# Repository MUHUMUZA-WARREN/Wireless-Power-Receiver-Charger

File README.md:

# Wireless-Power-Receiver---Charger
 5W resonant wireless power receiver and charger

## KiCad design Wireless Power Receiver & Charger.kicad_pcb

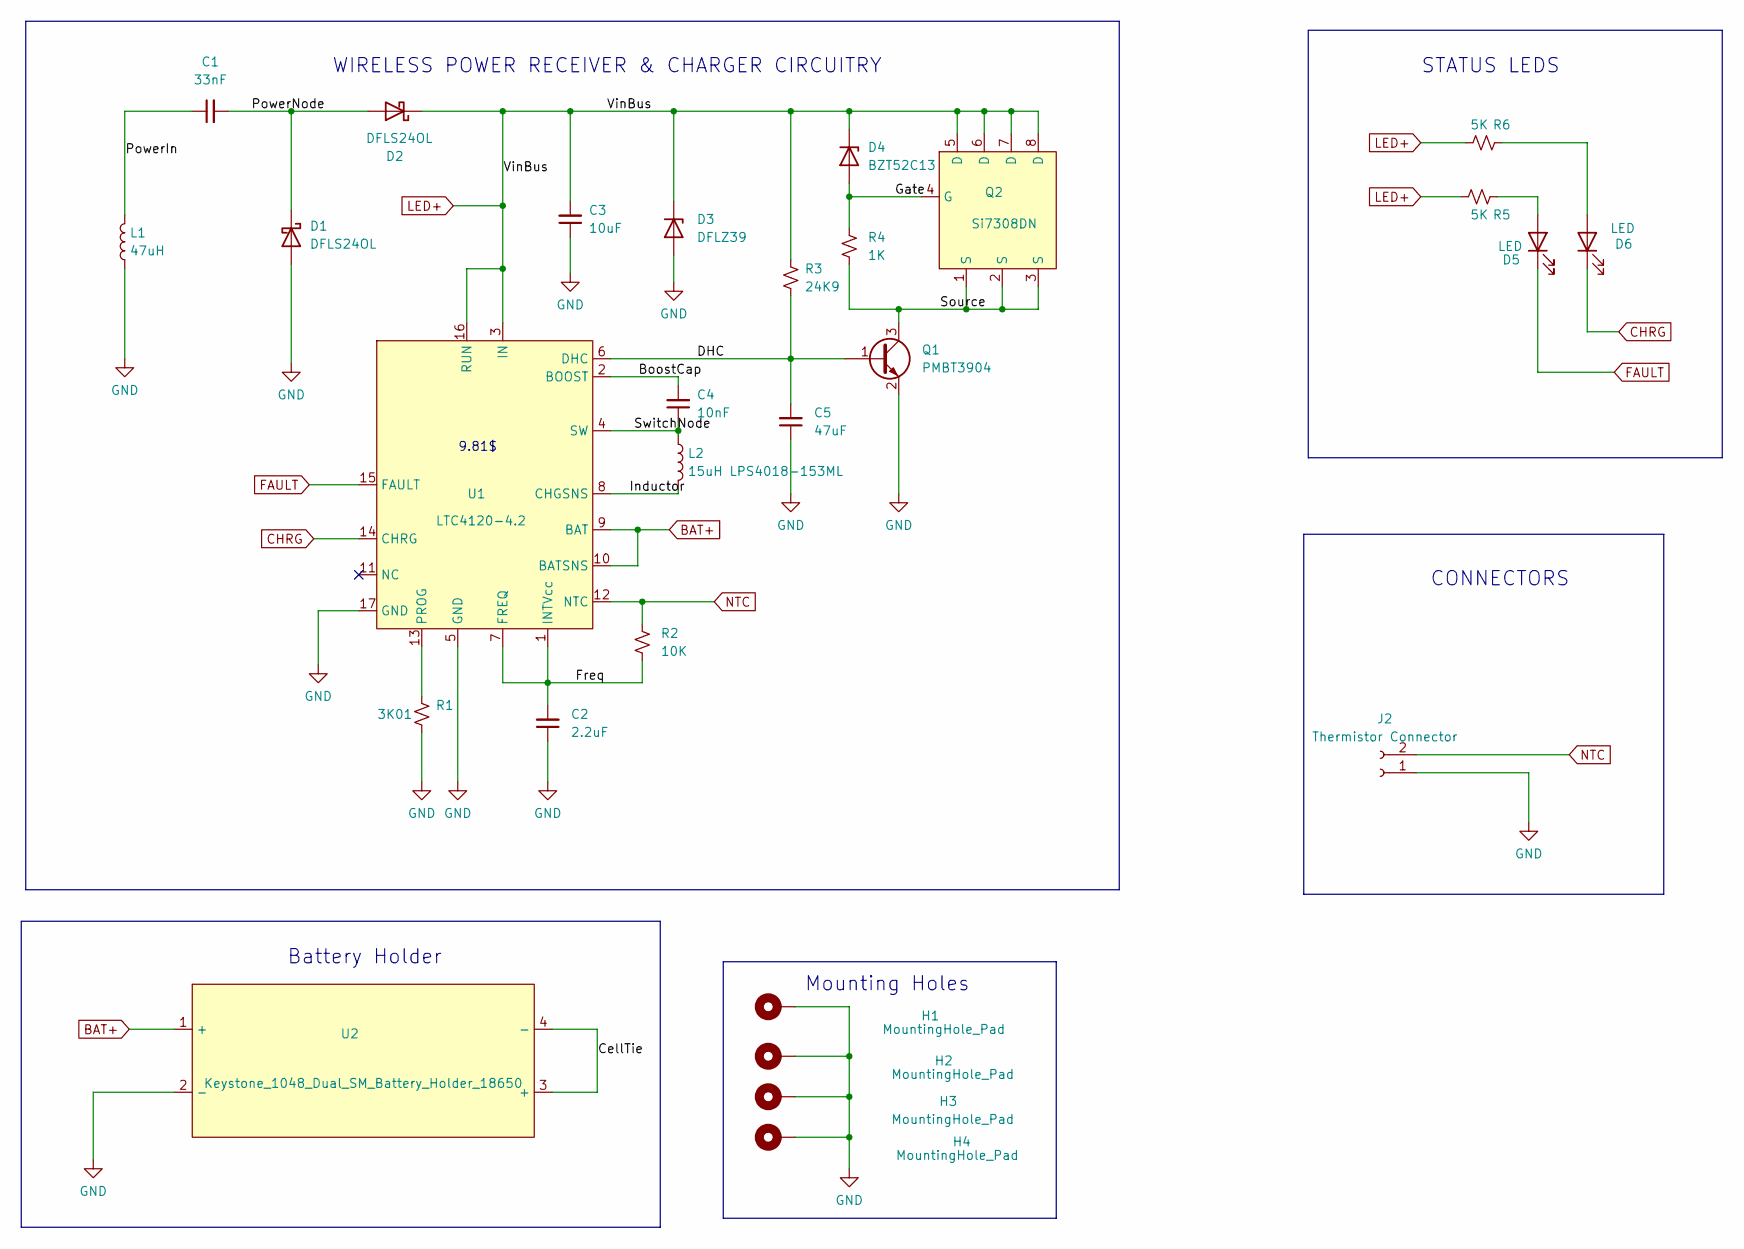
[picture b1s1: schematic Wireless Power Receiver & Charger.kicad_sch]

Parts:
C1: 33nF; C_1206_3216Metric
C2: 2.2uF; C_1206_3216Metric
C3: 10uF; C_1206_3216Metric
C4: 10nF; C_1206_3216Metric
C5: 47uF; C_0805_2012Metric
D1, D2: DFLS24OL; D_PowerDI-123
D3: DFLZ39; D_PowerDI-123
D4: BZT52C13; D_SOD-123
D5, D6: LED; LED_D1.8mm_W1.8mm_H2.4mm_Horizontal_O1.27mm_Z1.6mm
H1, H2, H3, H4: MountingHole_Pad; MountingHole_2.5mm_Pad_Via
J2: Thermistor Connector; JST_EH_B2B-EH-A_1x02_P2.50mm_Vertical
L1: 47uH; Tx Coil
L2: 15uH LPS4018-153ML; L_Coilcraft_LPS4018
Q1: PMBT3904; TSOT-23
Q2: Si7308DN; PowerPAK 1212-8 Single
R1: 3K01; R_1206_3216Metric
R2: 10K; R_1206_3216Metric
R3: 24K9; R_0805_2012Metric
R4: 1K; R_1206_3216Metric
R5, R6: 5K; R_1206_3216Metric
U1: LTC4120-4.2; QFN-16-1EP_4x4mm_P0.65mm_EP2.1x2.1mm_ThermalVias
U2: Keystone_1048_Dual_SM_Battery_Holder_18650; 1048 Dual SM Battery Holder 18650

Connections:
/BoostCap: C4.2, U1.2 (BOOST)
/CellTie: U2.3 (+), U2.4 (-)
/DHC: C5.2, Q1.1 (B), R3.2, U1.6 (DHC)
/Freq: C2.2, R2.2, U1.1 (INTVcc), U1.7 (FREQ)
/Gate: D4.2 (A), Q2.4 (G), R4.1
/Inductor: L2.2, U1.8 (CHGSNS)
/PowerIn: C1.1, L1.2
/PowerNode: C1.2, D1.1 (K), D2.2 (A)
/Source: Q1.3 (C), Q2.1 (S), Q2.2 (S), Q2.3 (S), R4.2
/SwitchNode: C4.1, L2.1, U1.4 (SW)
BAT+: U1.9 (BAT), U1.10 (BATSNS), U2.1 (+)
CHRG: D6.1 (K), U1.14 (CHRG)
FAULT: D5.1 (K), U1.15 (FAULT)
GND: C2.1, C3.1, C5.1, D1.2 (A), D3.2 (A), H1.1, H2.1, H3.1, H4.1, J2.1, L1.1, Q1.2 (E), R1.2, U1.5 (GND), U1.17 (GND), U2.2 (-)
LED+: C3.2, D2.1 (K), D3.1 (K), D4.1 (K), Q2.5 (D), Q2.6 (D), Q2.7 (D), Q2.8 (D), R3.1, R5.1, R6.1, U1.3 (IN), U1.16 (RUN)
NTC: J2.2, R2.1, U1.12 (NTC)
unnamed: D5.2 (A), R5.2
unnamed: D6.2 (A), R6.2
unnamed: R1.1, U1.13 (PROG)

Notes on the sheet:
CONNECTORS
Battery Holder
WIRELESS POWER RECEIVER & CHARGER CIRCUITRY
9.81$
STATUS LEDS
Mounting Holes

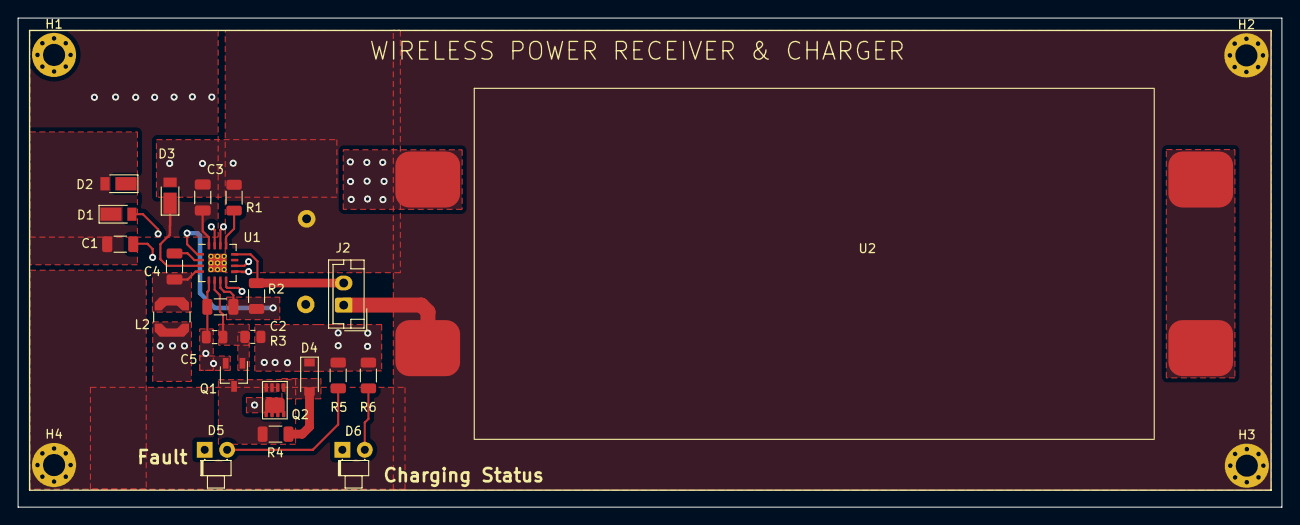
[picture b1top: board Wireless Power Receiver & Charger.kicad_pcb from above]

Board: 4 copper layers, 143.2 x 55.4 mm, 28 parts (1 on the bottom side), 19 nets.

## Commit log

2024-11-05 Update README.md
    Added an image to the readme file.
